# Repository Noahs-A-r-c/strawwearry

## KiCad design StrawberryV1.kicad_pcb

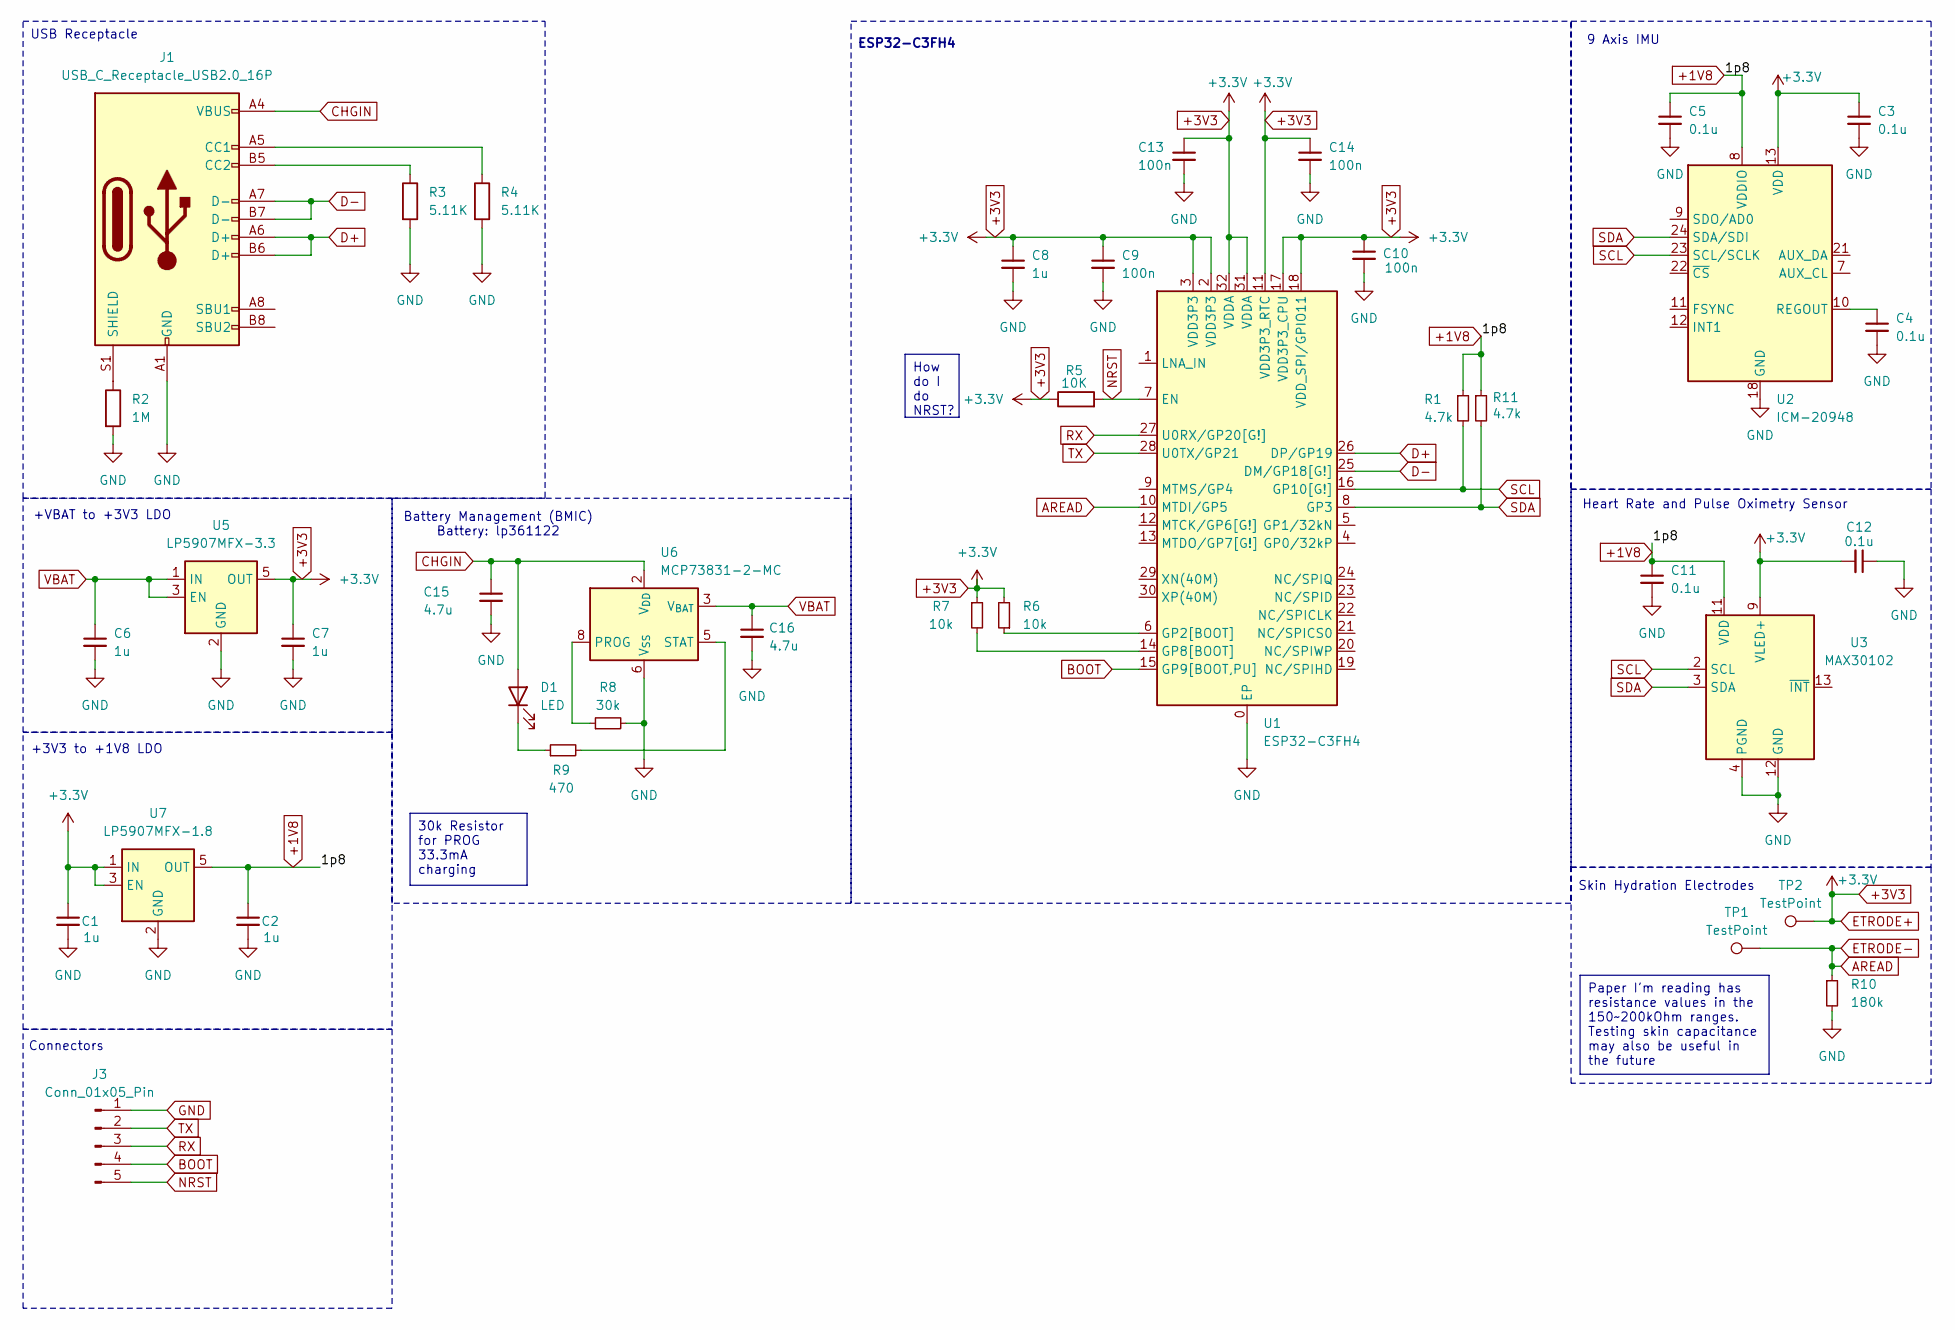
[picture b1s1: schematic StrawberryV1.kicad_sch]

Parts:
C1, C2, C6, C7, C8: 1u; C_0603_1608Metric
C3, C4, C5, C11, C12: 0.1u; C_0603_1608Metric
C9, C10, C13, C14: 100n; C_0603_1608Metric
C15, C16: 4.7u; C_0603_1608Metric
D1: LED; LED_0603_1608Metric
J1: USB_C_Receptacle_USB2.0_16P; USB_C_Receptacle_Palconn_UTC16-G
J3: Conn_01x05_Pin; PinSocket_1x05_P2.54mm_Vertical
R1, R11: 4.7k; R_0603_1608Metric
R2: 1M; R_0603_1608Metric
R3, R4: 5.11K; R_0603_1608Metric
R5: 10K; R_0603_1608Metric
R6, R7: 10k; R_0603_1608Metric
R8: 30k; R_0603_1608Metric
R9: 470; R_0603_1608Metric
R10: 180k; R_0603_1608Metric
TP1, TP2: TestPoint; PinHeader_1x01_P2.54mm_Vertical
U1: ESP32-C3FH4; Yu-QFN-32-5x5-0.5-EP-3.7x3.7
U2: ICM-20948; InvenSense_QFN-24_3x3mm_P0.4mm
U3: MAX30102; Maxim_OLGA-14_3.3x5.6mm_P0.8mm
U5: LP5907MFX-3.3; SOT-23-5
U6: MCP73831-2-MC; DFN-8-1EP_3x2mm_P0.5mm_EP1.7x1.4mm
U7: LP5907MFX-1.8; SOT-23-5

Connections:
+1V8: C2.1, C5.1, C11.1, R1.1, R11.1, U2.8 (VDDIO), U3.11 (VDD), U7.5 (OUT)
+3V3: C1.1, C3.1, C7.1, C8.1, C9.1, C10.1, C12.2, C13.1, C14.1, R5.1, R6.2, R7.1, TP2.1, U1.2 (VDD3P3), U1.3 (VDD3P3), U1.11 (VDD3P3_RTC), U1.17 (VDD3P3_CPU), U1.18 (VDD_SPI/GPIO11), U1.31 (VDDA), U1.32 (VDDA), U2.13 (VDD), U3.9 (VLED+), U3.10 (VLED+), U5.5 (OUT), U7.1 (IN), U7.3 (EN)
AREAD: R10.1, TP1.1, U1.10 (MTDI/GP5)
BOOT: J3.4, U1.15 (GP9[BOOT,PU])
CHGIN: C15.1, D1.2 (A), J1.A4 (VBUS), J1.A9 (VBUS), J1.B4 (VBUS), J1.B9 (VBUS), U6.1 (V_{DD}), U6.2 (V_{DD})
D+: J1.A6 (D+), J1.B6 (D+), U1.26 (DP/GP19)
D-: J1.A7 (D-), J1.B7 (D-), U1.25 (DM/GP18[G!])
GND: C1.2, C2.2, C3.2, C4.2, C5.2, C6.2, C7.2, C8.2, C9.2, C10.2, C11.2, C12.1, C13.2, C14.2, C15.2, C16.2, J1.A1 (GND), J1.A12 (GND), J1.B1 (GND), J1.B12 (GND), J3.1, R2.2, R3.2, R4.2, R8.2, R10.2, U1.0 (EP), U2.18 (GND), U2.20 (GND), U3.4 (PGND), U3.12 (GND), U5.2 (GND), U6.6 (V_{SS}), U7.2 (GND)
NRST: J3.5, R5.2, U1.7 (EN)
unnamed: D1.1 (K), R9.1
unnamed: J1.A5 (CC1), R4.1
unnamed: J1.B5 (CC2), R3.1
unnamed: J1.S1 (SHIELD), R2.1
unnamed: R6.1, U1.6 (GP2[BOOT])
unnamed: R7.2, U1.14 (GP8[BOOT])
unnamed: C4.1, U2.10 (REGOUT)
unnamed: R8.1, U6.8 (PROG)
unnamed: R9.2, U6.5 (STAT)
RX: J3.3, U1.27 (U0RX/GP20[G!])
SCL: R1.2, U1.16 (GP10[G!]), U2.23 (SCL/SCLK), U3.2 (SCL)
SDA: R11.2, U1.8 (GP3), U2.24 (SDA/SDI), U3.3 (SDA)
TX: J3.2, U1.28 (U0TX/GP21)
VBAT: C6.1, C16.1, U5.1 (IN), U5.3 (EN), U6.3 (V_{BAT}), U6.4 (V_{BAT})

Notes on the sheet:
30k Resistor for PROG 33.3mA charging
How do I do NRST?
Paper I'm reading has resistance values in the 150~200kOhm ranges. Testing skin capacitance may also be useful in the future
Skin Hydration Electrodes
Battery Management (BMIC) Battery: lp361122
Heart Rate and Pulse Oximetry Sensor
Connectors
ESP32-C3FH4
USB Receptacle
+3V3 to +1V8 LDO
9 Axis IMU
+VBAT to +3V3 LDO

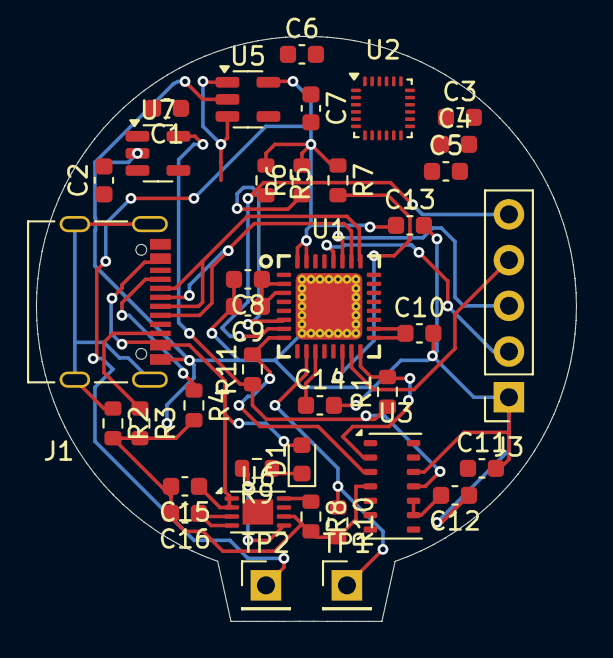
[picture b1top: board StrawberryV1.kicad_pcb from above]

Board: 2 copper layers, 30.0 x 32.5 mm, 38 parts (0 on the bottom side), 23 nets.

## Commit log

2024-04-23 first upload
2024-04-26 finished schematic
2024-04-29 update PCB unfinished
2024-04-29 PCB almost done
